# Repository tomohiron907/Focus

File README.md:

# Focus
A simple ortholinear keyborad.

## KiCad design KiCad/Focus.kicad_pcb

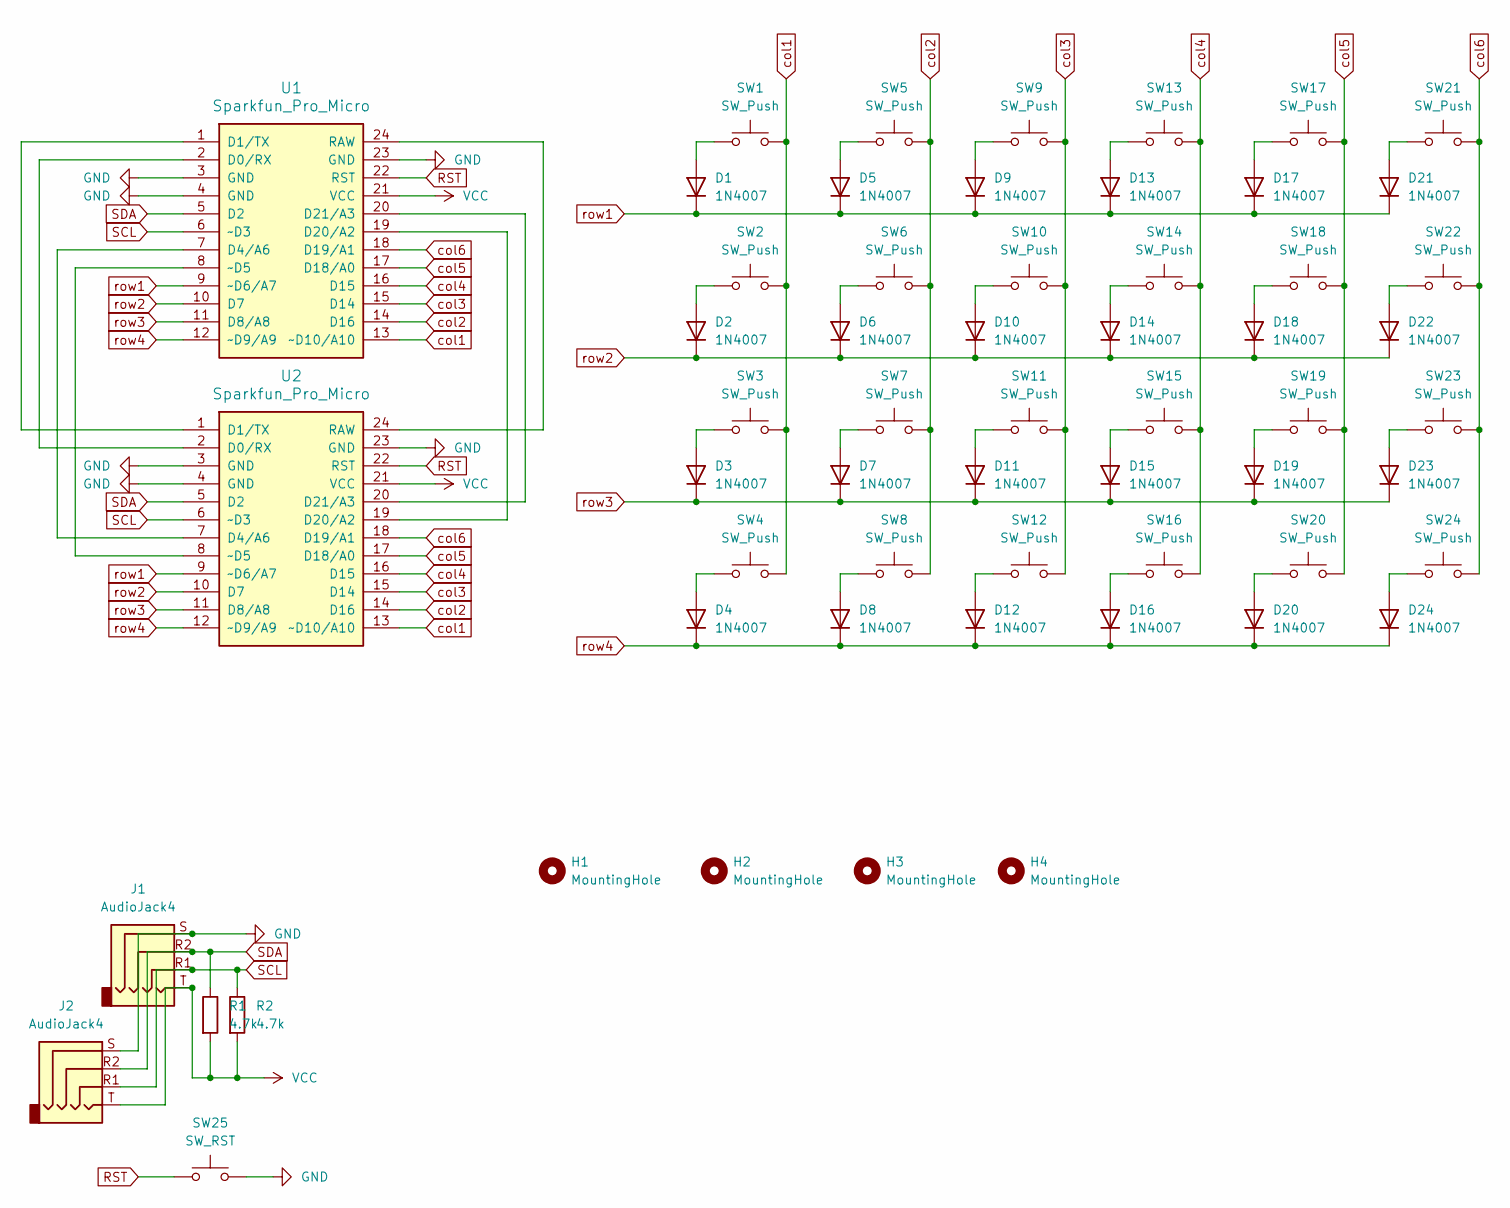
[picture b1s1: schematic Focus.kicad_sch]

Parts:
D1: 1N4007; Sparkfun_Pro_Micro
D2, D3, D4, D5, D6, D7, D8, D9, D10, D11, D12, D13, D14, D15, D16, D17, D18, D19, D20, D21, D22, D23, D24: 1N4007; D_DO-41_SOD81_P10.16mm_Horizontal
H1, H2, H3, H4: MountingHole; MountingHole_2.2mm_M2
J1, J2: AudioJack4; TRRS_Jack_3.5mm
R1, R2: 4.7k; R_Axial_DIN0207_L6.3mm_D2.5mm_P10.16mm_Horizontal
SW1, SW2, SW3, SW4, SW5, SW6, SW7, SW8, SW9, SW10, SW11, SW12, SW13, SW14, SW15, SW16, SW17, SW18, SW19, SW20, SW21, SW22, SW23, SW24: SW_Push; SW_MX_reversible
SW25: SW_RST; SW_PUSH_6mm_H4.3mm
U1, U2: Sparkfun_Pro_Micro

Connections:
GND: J1.S, J2.S, SW25.2, U1.3 (GND), U1.4 (GND), U1.23 (GND), U2.3 (GND), U2.4 (GND), U2.23 (GND)
unnamed: D1.2 (A), SW1.1
unnamed: D2.2 (A), SW2.1
unnamed: D3.2 (A), SW3.1
unnamed: D4.2 (A), SW4.1
unnamed: D5.2 (A), SW5.1
unnamed: D6.2 (A), SW6.1
unnamed: D7.2 (A), SW7.1
unnamed: D8.2 (A), SW8.1
unnamed: D9.2 (A), SW9.1
unnamed: D10.2 (A), SW10.1
unnamed: D11.2 (A), SW11.1
unnamed: D12.2 (A), SW12.1
unnamed: D13.2 (A), SW13.1
unnamed: D14.2 (A), SW14.1
unnamed: D15.2 (A), SW15.1
unnamed: D16.2 (A), SW16.1
unnamed: D17.2 (A), SW17.1
unnamed: D18.2 (A), SW18.1
unnamed: D19.2 (A), SW19.1
unnamed: D20.2 (A), SW20.1
unnamed: D21.2 (A), SW21.1
unnamed: D22.2 (A), SW22.1
unnamed: D23.2 (A), SW23.1
unnamed: D24.2 (A), SW24.1
unnamed: U1.1 (D1/TX), U2.1 (D1/TX)
unnamed: U1.2 (D0/RX), U2.2 (D0/RX)
unnamed: U1.7 (D4/A6), U2.7 (D4/A6)
unnamed: U1.8 (~D5), U2.8 (~D5)
unnamed: U1.19 (D20/A2), U2.19 (D20/A2)
unnamed: U1.20 (D21/A3), U2.20 (D21/A3)
unnamed: U1.24 (RAW), U2.24 (RAW)
RST: SW25.1, U1.22 (RST), U2.22 (RST)
SCL: J1.R1, J2.R1, R2.1, U1.6 (~D3), U2.6 (~D3)
SDA: J1.R2, J2.R2, R1.1, U1.5 (D2), U2.5 (D2)
VCC: J1.T, J2.T, R1.2, R2.2, U1.21 (VCC), U2.21 (VCC)
col1: SW1.2, SW2.2, SW3.2, SW4.2, U1.13 (~D10/A10), U2.13 (~D10/A10)
col2: SW5.2, SW6.2, SW7.2, SW8.2, U1.14 (D16), U2.14 (D16)
col3: SW9.2, SW10.2, SW11.2, SW12.2, U1.15 (D14), U2.15 (D14)
col4: SW13.2, SW14.2, SW15.2, SW16.2, U1.16 (D15), U2.16 (D15)
col5: SW17.2, SW18.2, SW19.2, SW20.2, U1.17 (D18/A0), U2.17 (D18/A0)
col6: SW21.2, SW22.2, SW23.2, SW24.2, U1.18 (D19/A1), U2.18 (D19/A1)
row1: D1.1 (K), D5.1 (K), D9.1 (K), D13.1 (K), D17.1 (K), D21.1 (K), U1.9 (~D6/A7), U2.9 (~D6/A7)
row2: D2.1 (K), D6.1 (K), D10.1 (K), D14.1 (K), D18.1 (K), D22.1 (K), U1.10 (D7), U2.10 (D7)
row3: D3.1 (K), D7.1 (K), D11.1 (K), D15.1 (K), D19.1 (K), D23.1 (K), U1.11 (D8/A8), U2.11 (D8/A8)
row4: D4.1 (K), D8.1 (K), D12.1 (K), D16.1 (K), D20.1 (K), D24.1 (K), U1.12 (~D9/A9), U2.12 (~D9/A9)

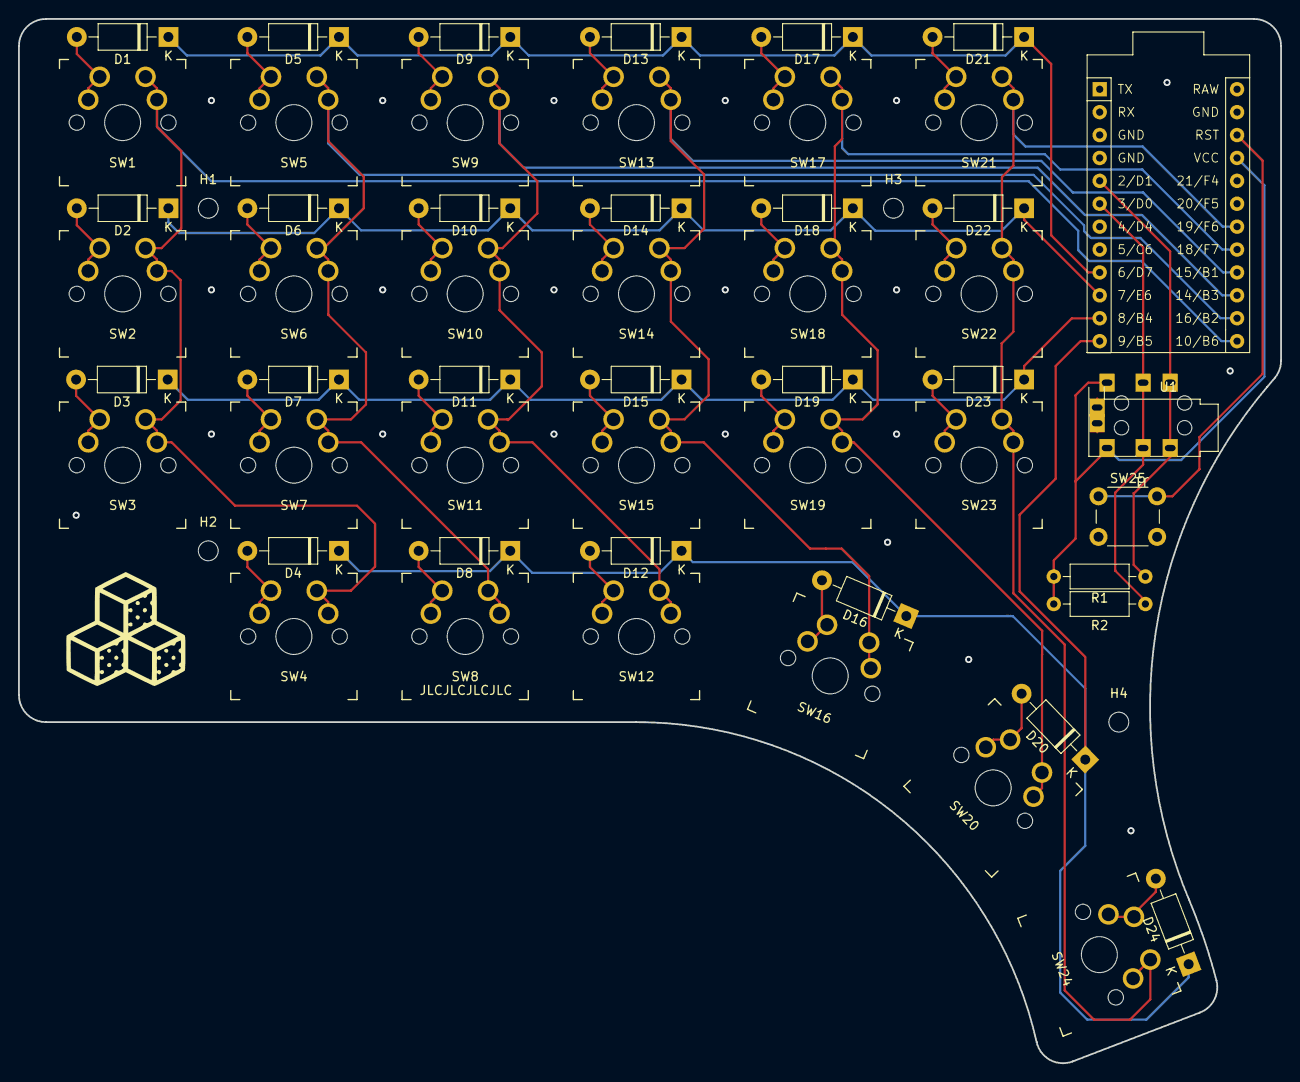
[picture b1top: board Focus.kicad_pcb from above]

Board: 2 copper layers, 140.0 x 115.8 mm, 58 parts (1 on the bottom side), 39 nets.

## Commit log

2023-12-23 add files
2023-12-24 add image to README
2023-12-27 changed keymaps
2024-01-02 add via files
2024-01-10 update firmware
2024-01-10 fix typo
